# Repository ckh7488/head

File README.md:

# R5 로봇 헤드

R5는 코에 숨긴 카메라로 지나가는 사람을 보고, 눈이 먼저 움직인 뒤 목이 천천히 따라가는 **6축 해골 로봇**입니다. PC가 얼굴을 찾고 OpenRB-150이 모터 여섯 축을 제어합니다. 전시 모드에서는 눈을 깜빡이며, 턱은 별도 시연 모드에서 움직입니다.

현재 제작 자료는 **B26 기구와 A5 서보 허브** 기준입니다. P2S PETG HF 출력은 **18판·55개**입니다. 168단계 조립 경로를 CAD로 검사했으며, 최종 체결·배선과 구동은 P01–P08 실물 시험에서 확인합니다. [B26 제작 자료](mechanical/revisions/b26/) · [조립 절차](mechanical/revisions/b26/assembly.md)

## 제작 순서

| 순서 | 할 일 |
| --- | --- |
| 1. 출력 준비 | 핀·베어링·나사를 준비합니다. 한 번에 맡길 때는 **15번 링크 판**으로 바닥 접지를 확인한 뒤 **13번 턱 판**으로 큰 부품의 출력 상태를 확인합니다. [출력과 후가공](mechanical/revisions/b25/01-seoul-print.md) · [먼저 살 부품](mechanical/revisions/b25/02-order-before.md) |
| 2. 건식 맞춤 | 전원과 접착제 없이 끼움과 공구 접근을 봅니다. 턱을 연 채 오른쪽 받침과 요크 사이에 0.30 mm 틈새 게이지가 통과하는지 확인합니다. [건식 맞춤](mechanical/revisions/b25/01-seoul-print.md#출력물-후가공과-건식-맞춤) · [치수 선택용 게이지](mechanical/revisions/b25/fit-gauge.md) |
| 3. 모터·전장 구매 | 건식 맞춤을 마친 뒤 모터·카메라·A5 허브를 준비합니다. [시험 뒤 구매](mechanical/revisions/b25/03-order-after.md) · [A5 PCBA 발주](electronics/README.md#jlcpcb-밑면-실장) |
| 4. 허브 첫 통전 | 허브를 받침에 넣기 전에 작업대에서 확인합니다. 모터·OpenRB·퓨즈를 뺍니다. 무전원 도통 확인과 J2 잠금을 마친 뒤 입력 전압부터 확인합니다. [전원 실물 검수](electronics/README.md#전원-실물-검수) |
| 5. 조립과 보정 | 허브의 전원을 뽑고 조립·배선합니다. 무전원에서 배선을 확인하고, 전원을 켜서 한 축씩 보정합니다. [B26 조립 절차](mechanical/revisions/b26/assembly.md) · [구동과 보정](control/README.md) |
| 6. 실물 인수 | 완성품의 조립 상태, 움직임, 전압과 전원 복구를 확인합니다. [실물 시험 P01–P08](spec/bench.md#b25-실물-시험) |

## 주요 사양

| 항목 | B26 적용값 |
| --- | --- |
| 머리 외형과 환경 | 약 `160 × 166 × 167 mm`, 한국 실내 `−5–35 °C` |
| 3D 프린팅 | **Bambu Lab P2S** (0.4 mm 경화 노즐), **Bambu PETG HF** (65 °C 4–6시간 건조 · 2롤), 18판·55개 |
| 눈과 턱 (5 V) | ID1–ID3 `XL330-M077-T` × 3, ID6 `XL330-M288-T` × 1 |
| 목 (12 V) | ID4·ID5 `XL430-W250-T` × 2 |
| 카메라와 제어 | `U20CAM-1080P-S1`, `OpenRB-150` (USB 전원), `A5 서보 허브` |

## 파일과 기준

- [A5 회로도·PCB·3D 단일 HTML](web/b25/R5-B25-A5.html)
- [FreeCAD 조립본](mechanical/revisions/b26/R5-B26-Assembly.FCStd) · [P2S PETG HF 출력 프로젝트](mechanical/revisions/b26/R5-B26-P2S.3mf) · [B26 오프라인 3D 조립](web/b26/R5-B26-assembly.html) · [3D 조립·구동·배선 화면 만들기](web/README.md#b26-웹-화면)
- [1층 사람 요구사항](spec/user-spec.md) · [2층 수치 기준](spec/conditions.md) · [FDM 실수 모음집](spec/fdm-pitfalls.md) · [동작 인수 기준](spec/requirements.md)
- [기구 자료](mechanical/README.md) · [전장 자료](electronics/README.md) · [하드웨어 없이 테스트](control/README.md#하드웨어-없이-실행) · [이전 리비전](mechanical/revisions/)

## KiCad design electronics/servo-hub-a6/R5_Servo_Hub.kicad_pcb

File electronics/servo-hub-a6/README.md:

# B25 A6 서보 허브

전 부품을 직접 납땜하는 4층 시안입니다. 기판 앞쪽을 2 mm 늘려 70 × 37 mm로 만들고, 밑면의 보호 칩 세 개를 한 줄로 배치했습니다. H1–H4와 J1–J8의 위치·홀·핀 연결은 A5와 같습니다. [오프라인 뷰어](../../web/b25/R5-B25-A6.html) · [회로도](R5_Servo_Hub.kicad_sch) · [PCB](R5_Servo_Hub.kicad_pcb) · [전체 BOM](BOM.csv)

## 납땜과 주문

1. Gerber로 **FR-4 1.6 mm · 4층 · 외층 1 oz · 내층 0.5 oz · 녹색 · 무연 HASL** 생기판을 견적 냅니다. [Gerber·드릴](../fabrication/R5_Servo_Hub_A6-Gerbers.zip) · [JLCPCB 기판 규격](https://jlcpcb.com/capabilities/pcb-capabilities)
2. 밑면 SMD 12개를 먼저 납땜합니다. U1–U3은 다리가 보이는 **TPS25221DBVR, SOT-23-6, 피치 0.95 mm**입니다. 세 칩의 방향은 같으며 HTML의 밑면 그림에 1번 핀이 표시됩니다. R4–R6은 **30.9 kΩ, ±0.1%, ≤25 ppm/°C, 0805**, C3–C5는 **100 nF, 0805, 몸체 높이 1.45 mm 이하**입니다. [TI 데이터시트와 패키지 도면](https://www.ti.com/lit/ds/symlink/tps25221.pdf)
3. 윗면 관통홀 14개를 끼운 뒤 밑면에서 납땜합니다. XT30과 퓨즈 홀더에는 열 회복이 빠른 온도조절 인두와 2.4 mm 안팎의 평팁을 씁니다. F1·F2, 모터와 OpenRB를 뺀 채 5 V와 12 V 입력을 하나씩 검수합니다. [전원 실물 검수](../README.md#전원-실물-검수)

## 검사 결과

- KiCad ERC, DRC, 회로도와 PCB 일치 검사에서 위반 0건입니다.
- 기존 B25 FreeCAD 조립에서 확장한 기판과 새 밑면 SMD 9개의 외형을 넣고, 밑면 덮개 30 mm 하강 경로를 확인했습니다. 기판 외곽과 배치 공차를 포함한 검사에서 기판과 베이스의 겹침은 없었고, 새 부품과 덮개의 최소 간격은 **0.565 mm**였습니다. [B25 조립 CAD](../../mechanical/revisions/b25/R5-B25-Assembly.FCStd)
- 공칭 5 V와 카탈로그 정지전류를 동시에 적용한 보수적 모델에서 최저 모터 단자 전압은 **4.025 V**입니다. 같은 계산에서 A5는 **4.132 V**입니다. TPS25221 자체의 전형 저항은 70 mΩ로 TPS2557의 22 mΩ보다 높습니다. 1.47 A에서 칩 하나의 전압강하는 약 71 mV 늘고 전형 손실은 약 0.05 W에서 0.15 W로 늘어납니다. 칩의 권장 입력 상한은 6.5 V에서 5.5 V로 낮아집니다. 30.9 kΩ 설정의 데이터시트 전류 제한 범위는 1.626–1.907 A입니다. 첫 시제품에서 동작 중 전압, 보호 칩 온도와 전류 제한에 걸리는지 확인합니다. [P07 실물 시험](../../spec/bench.md#p07-카메라-왕복과-전원)

기판 제작 파일은 첫 명령으로 만듭니다. HTML을 재생성하려면 결과 Gerber ZIP을 `electronics/fabrication/`에 두고 KiCad 9의 3D 모델과 `npm ci --prefix web`을 준비합니다. XT30 STEP은 A5 문서의 원본 모델 규격을 따릅니다. [XT30 STEP 좌표](../servo-hub-a5/#검증)

```sh
/usr/bin/python3 electronics/export.py servo-hub-a6
/usr/bin/python3 electronics/power_check.py --hub-revision A6
/usr/bin/python3 web/wiring-review/a4/build.py --hub-revision A6 --xt30-step /path/to/XT30PW-M.step build/R5-B25-A6.html
```

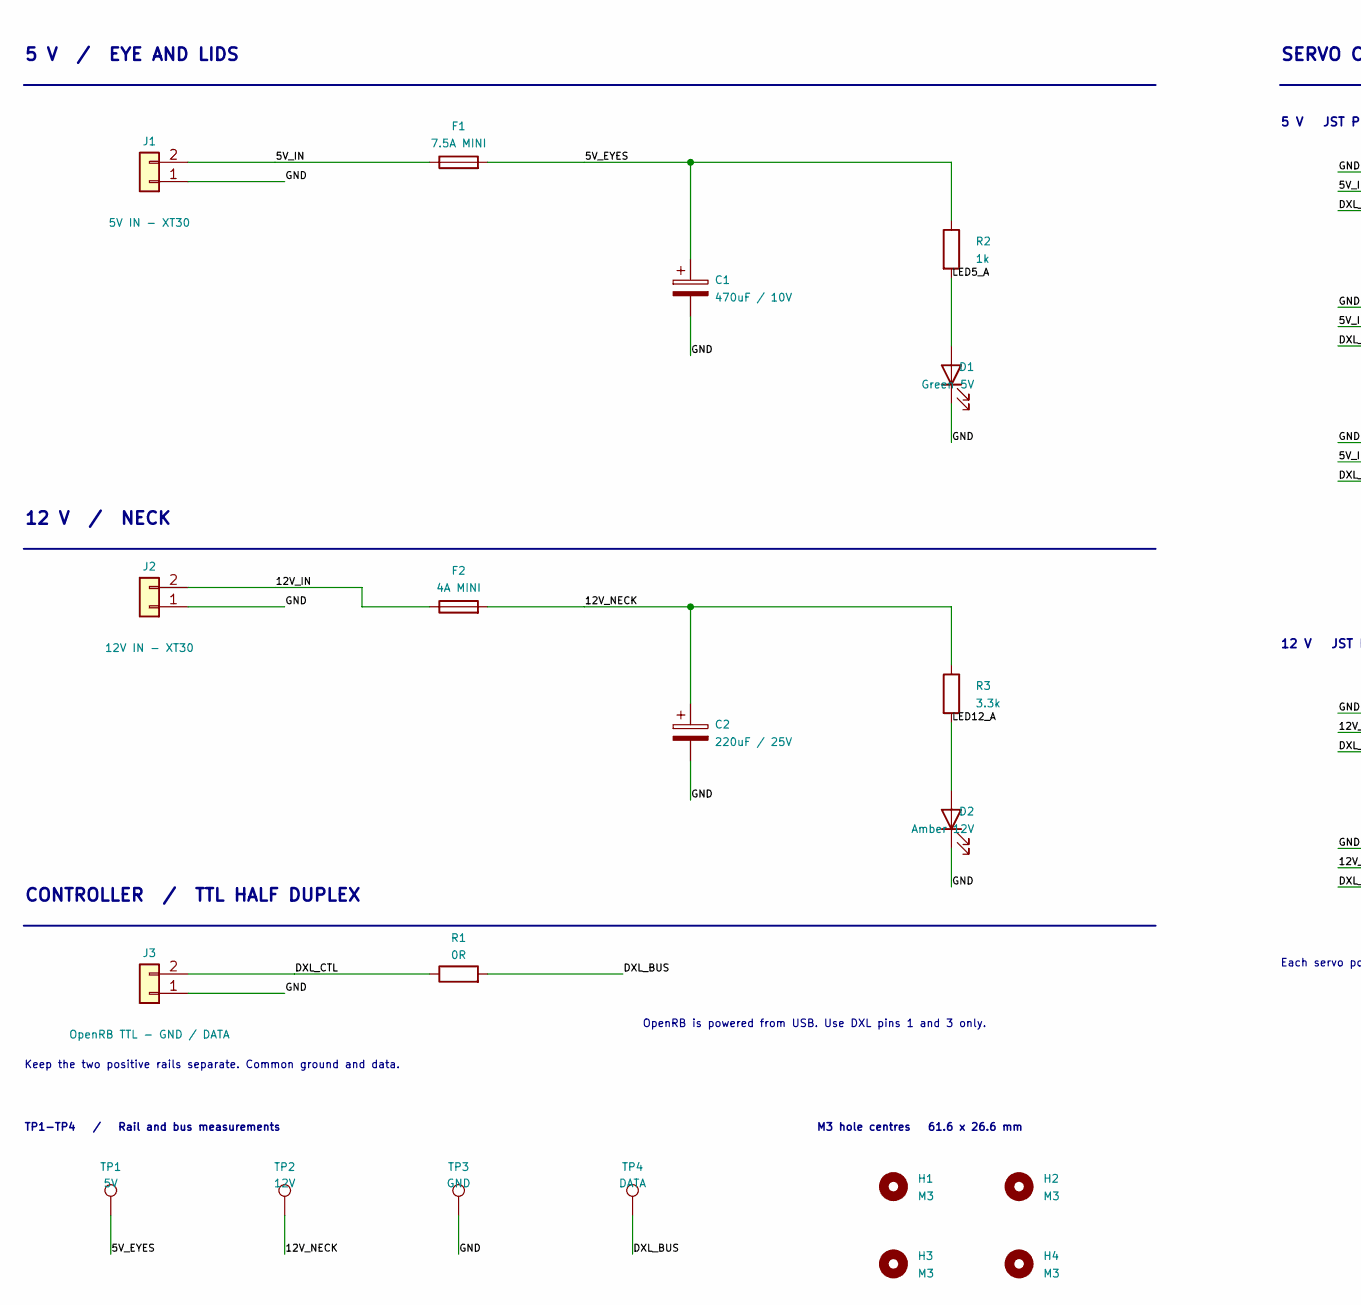
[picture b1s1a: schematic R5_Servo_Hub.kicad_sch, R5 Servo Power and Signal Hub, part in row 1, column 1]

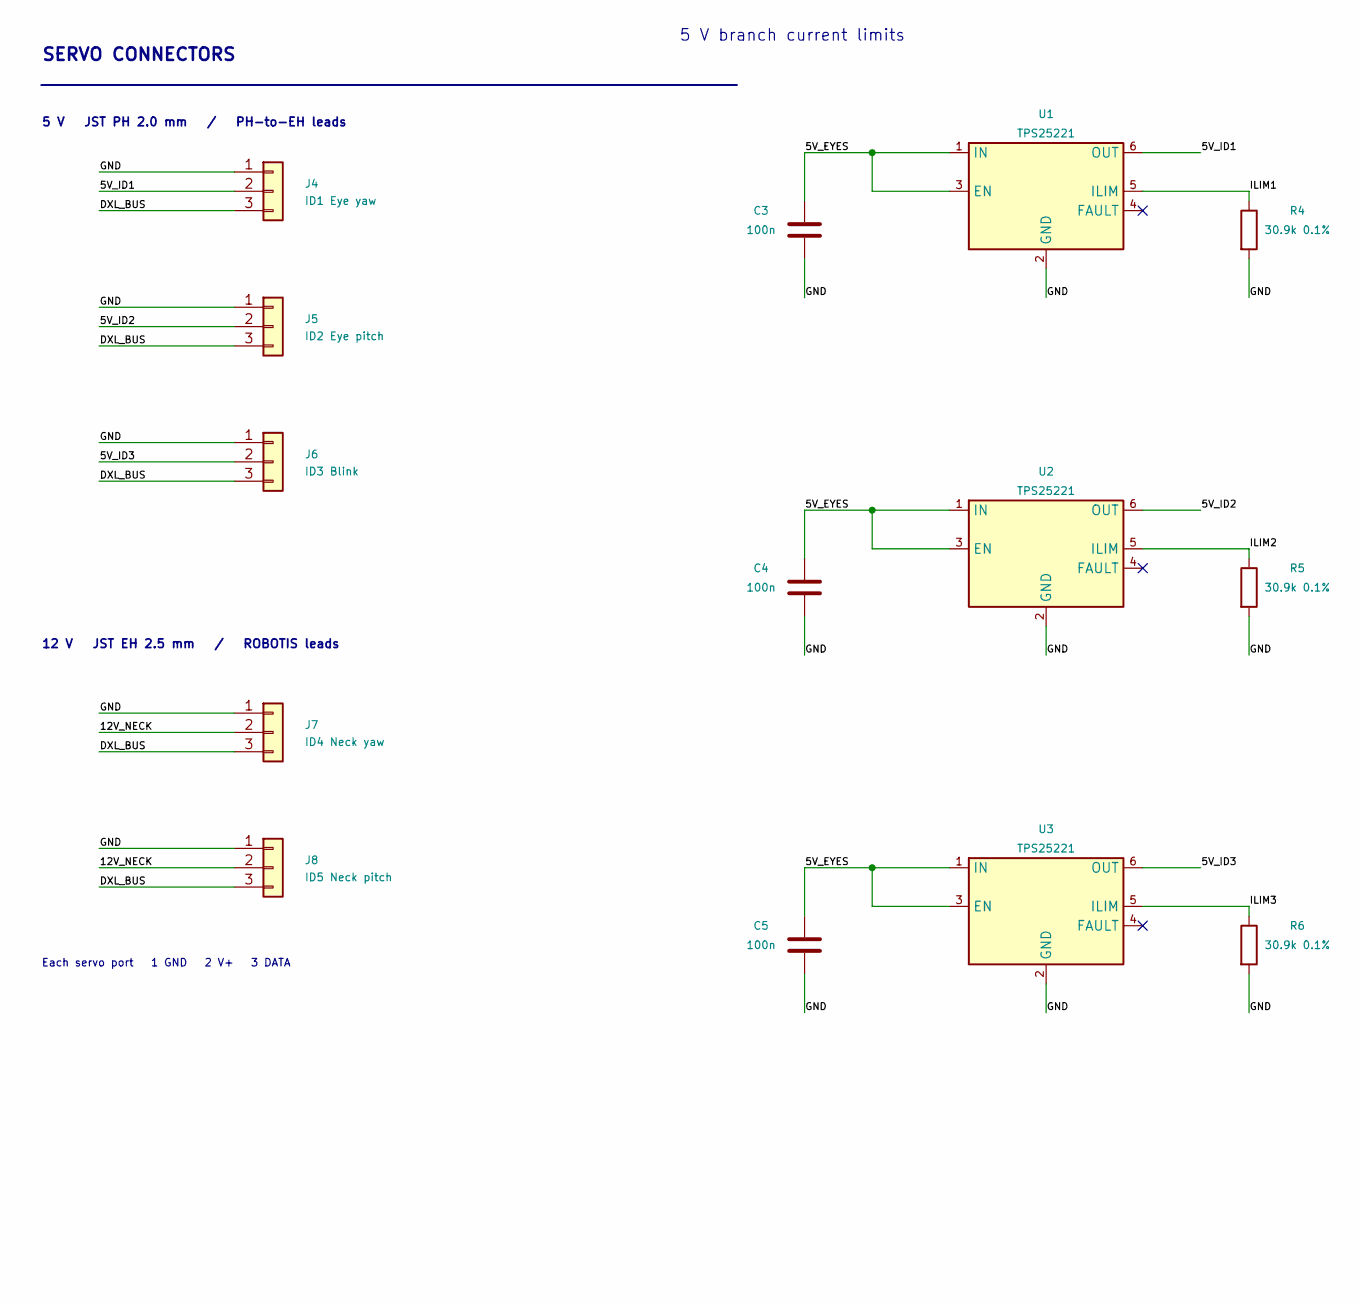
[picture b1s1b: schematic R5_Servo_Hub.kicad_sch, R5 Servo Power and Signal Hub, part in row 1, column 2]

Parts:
C1: 470uF / 10V; CP_Radial_D8.0mm_P3.50mm
C2: 220uF / 25V; CP_Radial_D8.0mm_P3.50mm
C3, C4, C5: 100n; C_0805_2012Metric
D1: Green 5V; LED_D3.0mm
D2: Amber 12V; LED_D3.0mm
F1: 7.5A MINI; Fuseholder_Blade_Mini_Keystone_3568
F2: 4A MINI; Fuseholder_Blade_Mini_Keystone_3568
H1, H2, H3, H4: M3; MountingHole_3.2mm_M3
J1: 5V IN - XT30; AMASS_XT30PW-M_1x02_P5.00mm_Horizontal_J1
J2: 12V IN - XT30; AMASS_XT30PW-M_1x02_P5.00mm_Horizontal
J3: OpenRB TTL - GND / DATA; JST_PH_B2B-PH-K_1x02_P2.00mm_Vertical
J4: ID1 Eye yaw; JST_PH_B3B-PH-K_1x03_P2.00mm_Vertical
J5: ID2 Eye pitch; JST_PH_B3B-PH-K_1x03_P2.00mm_Vertical
J6: ID3 Blink; JST_PH_B3B-PH-K_1x03_P2.00mm_Vertical
J7: ID4 Neck yaw; JST_EH_B3B-EH-A_1x03_P2.50mm_Vertical
J8: ID5 Neck pitch; JST_EH_B3B-EH-A_1x03_P2.50mm_Vertical
R1: 0R; R_1206_3216Metric
R2: 1k; R_1206_3216Metric
R3: 3.3k; R_0805_2012Metric
R4, R5, R6: 30.9k 0.1%; R_0805_2012Metric
TP1: 5V; TestPoint_THTPad_D2.0mm_Drill1.0mm
TP2: 12V; TestPoint_THTPad_D2.0mm_Drill1.0mm
TP3: GND; TestPoint_THTPad_D2.0mm_Drill1.0mm
TP4: DATA; TestPoint_THTPad_D2.0mm_Drill1.0mm
U1, U2, U3: TPS25221; SOT-23-6

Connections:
/5V_EYES: C1.1, C3.1, C4.1, C5.1, F1.2, R2.1, TP1.1, U1.1 (IN), U1.3 (EN), U2.1 (IN), U2.3 (EN), U3.1 (IN), U3.3 (EN)
/5V_ID1: J4.2, U1.6 (OUT)
/5V_ID2: J5.2, U2.6 (OUT)
/5V_ID3: J6.2, U3.6 (OUT)
/5V_IN: F1.1, J1.2
/12V_IN: F2.1, J2.2
/12V_NECK: C2.1, F2.2, J7.2, J8.2, R3.1, TP2.1
/DXL_BUS: J4.3, J5.3, J6.3, J7.3, J8.3, R1.2, TP4.1
/DXL_CTL: J3.2, R1.1
/GND: C1.2, C2.2, C3.2, C4.2, C5.2, D1.1 (K), D2.1 (K), J1.1, J2.1, J3.1, J4.1, J5.1, J6.1, J7.1, J8.1, R4.2, R5.2, R6.2, TP3.1, U1.2 (GND), U2.2 (GND), U3.2 (GND)
/ILIM1: R4.1, U1.5 (ILIM)
/ILIM2: R5.1, U2.5 (ILIM)
/ILIM3: R6.1, U3.5 (ILIM)
/LED5_A: D1.2 (A), R2.2
/LED12_A: D2.2 (A), R3.2

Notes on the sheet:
5 V / EYE AND LIDS
12 V / NECK
CONTROLLER / TTL HALF DUPLEX
SERVO CONNECTORS
5 V JST PH 2.0 mm / PH-to-EH leads
12 V JST EH 2.5 mm / ROBOTIS leads
Each servo port 1 GND 2 V+ 3 DATA
TP1-TP4 / Rail and bus measurements
M3 hole centres 61.6 x 26.6 mm
OpenRB is powered from USB. Use DXL pins 1 and 3 only.
Keep the two positive rails separate. Common ground and data.
5 V branch current limits

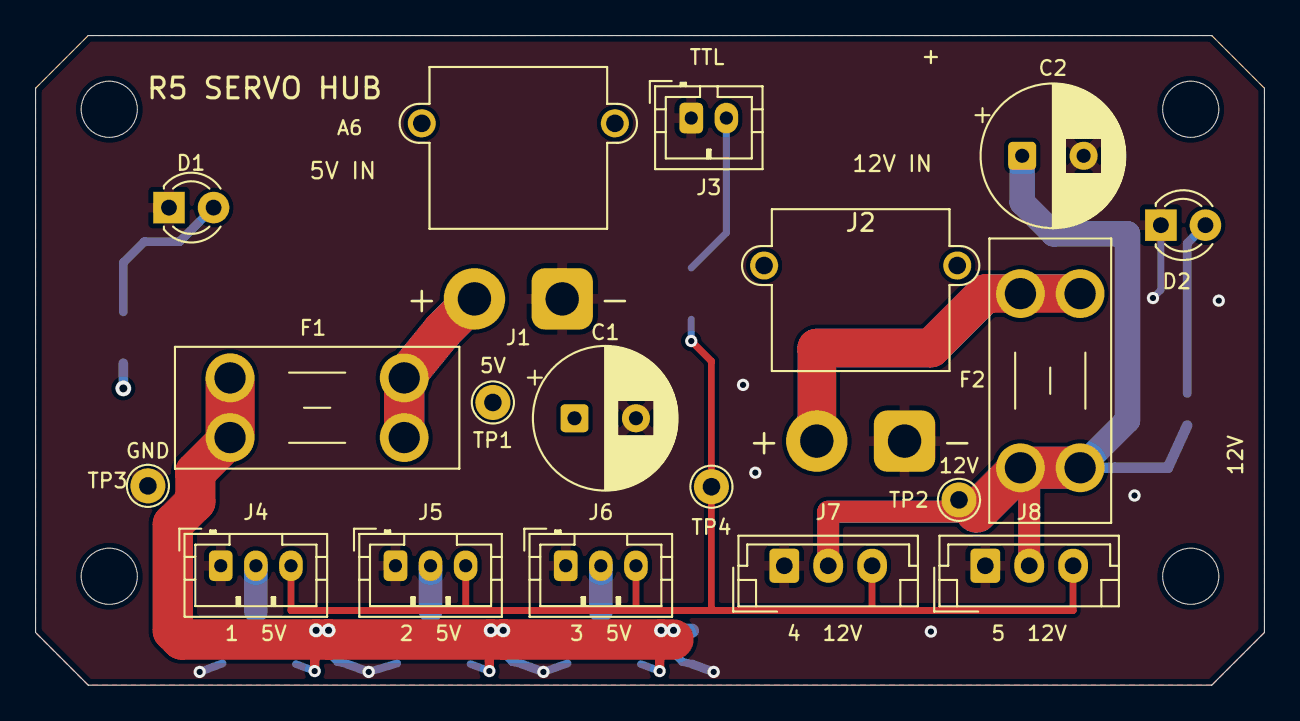
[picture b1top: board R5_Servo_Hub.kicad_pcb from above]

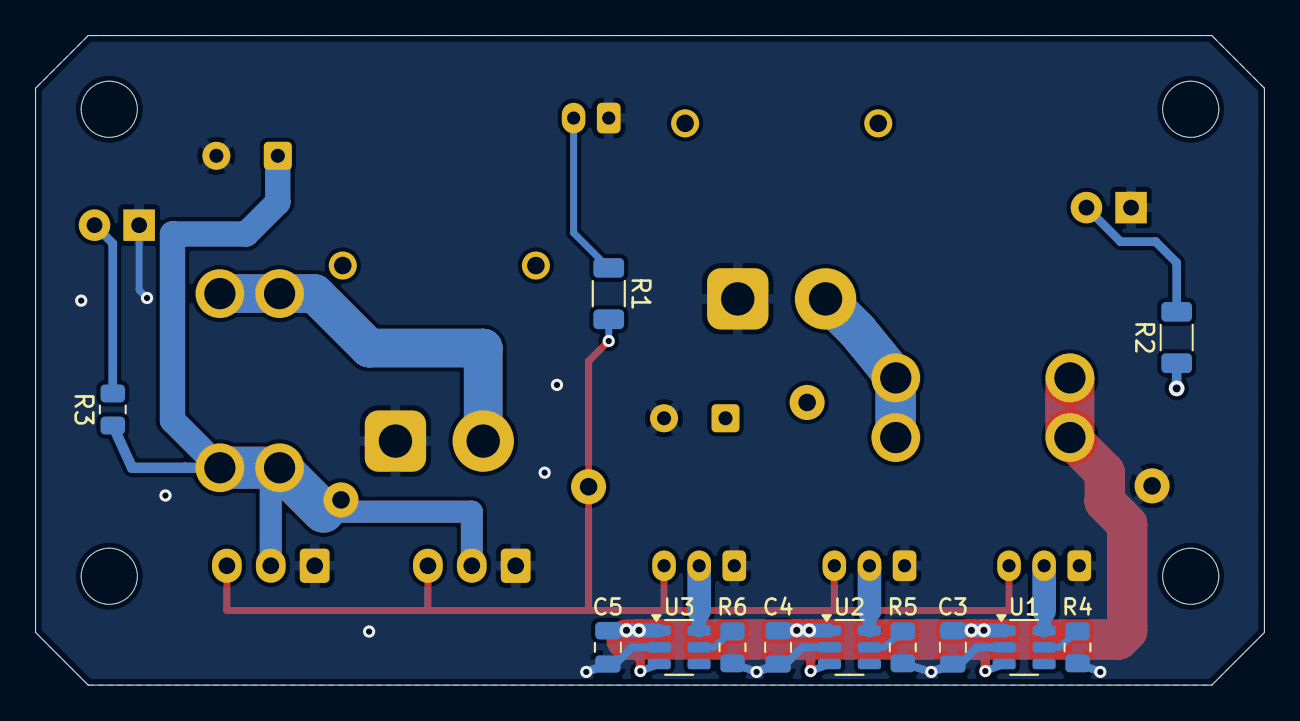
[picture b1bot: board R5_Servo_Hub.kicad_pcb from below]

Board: 4 copper layers, 70.0 x 37.0 mm, 34 parts (12 on the bottom side), 15 nets.

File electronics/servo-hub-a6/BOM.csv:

Ref,Value,Footprint,Populate,Part or buying specification,Notes
C1,470uF / 10V,Capacitor_THT:CP_Radial_D8.0mm_P3.50mm,YES,Panasonic EEU-FR1A471,"470 µF / 10 V, Ø8 × 11.5 mm, P3.5 mm. Match polarity."
C2,220uF / 25V,Capacitor_THT:CP_Radial_D8.0mm_P3.50mm,YES,Panasonic EEU-FR1E221,"220 µF / 25 V, Ø8 × 11.5 mm, P3.5 mm. Match polarity."
C3,100n,Capacitor_SMD:C_0805_2012Metric,YES,"100 nF X7R ±10% 50 V, 0805","Body height 1.45 mm max, 50 V, X7R, ±10% local input bypass"
C4,100n,Capacitor_SMD:C_0805_2012Metric,YES,"100 nF X7R ±10% 50 V, 0805","Body height 1.45 mm max, 50 V, X7R, ±10% local input bypass"
C5,100n,Capacitor_SMD:C_0805_2012Metric,YES,"100 nF X7R ±10% 50 V, 0805","Body height 1.45 mm max, 50 V, X7R, ±10% local input bypass"
D1,Green 5V,LED_THT:LED_D3.0mm,YES,3 mm diffused through-hole LED Green,"P2.54 mm, cathode pin 1"
D2,Amber 12V,LED_THT:LED_D3.0mm,YES,3 mm diffused through-hole LED Amber,"P2.54 mm, cathode pin 1"
F1,7.5A MINI,Fuse:Fuseholder_Blade_Mini_Keystone_3568,YES,Keystone 3568 + Littelfuse 029707.5L (7.5 A),Common 5 V feed
F2,4A MINI,Fuse:Fuseholder_Blade_Mini_Keystone_3568,YES,Keystone 3568 + Littelfuse 0297004.WXNV (4 A),12 V branch
H1,M3,MountingHole:MountingHole_3.2mm_M3,NATIVE,Bare pad or drilled mounting hole,No part
H2,M3,MountingHole:MountingHole_3.2mm_M3,NATIVE,Bare pad or drilled mounting hole,No part
H3,M3,MountingHole:MountingHole_3.2mm_M3,NATIVE,Bare pad or drilled mounting hole,No part
H4,M3,MountingHole:MountingHole_3.2mm_M3,NATIVE,Bare pad or drilled mounting hole,No part
J1,5V IN - XT30,R5_Hub:AMASS_XT30PW-M_1x02_P5.00mm_Horizontal_J1,YES,Amass XT30PW-M,"Pad 2 positive, pad 1 GND"
J2,12V IN - XT30,R5_Hub:AMASS_XT30PW-M_1x02_P5.00mm_Horizontal,YES,AMASS XT30PW-M,"Pad 2 positive, pad 1 GND. Mate with captive labeled 12 V XT30U-F."
J3,OpenRB TTL - GND / DATA,R5_Hub:JST_PH_B2B-PH-K_1x02_P2.00mm_Vertical,YES,JST B2B-PH-K-S,"EH1 to PH1, EH3 to PH2, no wire on EH2"
J4,ID1 Eye yaw,R5_Hub:JST_PH_B3B-PH-K_1x03_P2.00mm_Vertical,YES,JST B3B-PH-K-S,"5 V output, fit PH-to-EH lead"
J5,ID2 Eye pitch,R5_Hub:JST_PH_B3B-PH-K_1x03_P2.00mm_Vertical,YES,JST B3B-PH-K-S,"5 V output, fit PH-to-EH lead"
J6,ID3 Blink,R5_Hub:JST_PH_B3B-PH-K_1x03_P2.00mm_Vertical,YES,JST B3B-PH-K-S,"5 V output, fit PH-to-EH lead"
J7,ID4 Neck yaw,Connector_JST:JST_EH_B3B-EH-A_1x03_P2.50mm_Vertical,YES,JST B3B-EH-A,12 V output
J8,ID5 Neck pitch,Connector_JST:JST_EH_B3B-EH-A_1x03_P2.50mm_Vertical,YES,JST B3B-EH-A,12 V output
R1,0R,Resistor_SMD:R_1206_3216Metric,YES,Uniroyal 1206W4F0000T5E,"0 Ω data link, hand solder on bottom"
R2,1k,Resistor_SMD:R_1206_3216Metric,YES,Uniroyal 1206W4F1001T5E,"1 kΩ, 1%, 250 mW, hand solder on bottom"
R3,3.3k,Resistor_SMD:R_0805_2012Metric,YES,Uniroyal 0805W8F3301T5E,"3.3 kΩ, 1%, 125 mW, hand solder on bottom"
R4,30.9k 0.1%,Resistor_SMD:R_0805_2012Metric,YES,"30.9 kΩ, ±0.1%, ≤25 ppm/°C, 0805",Per-channel current limit
R5,30.9k 0.1%,Resistor_SMD:R_0805_2012Metric,YES,"30.9 kΩ, ±0.1%, ≤25 ppm/°C, 0805",Per-channel current limit
R6,30.9k 0.1%,Resistor_SMD:R_0805_2012Metric,YES,"30.9 kΩ, ±0.1%, ≤25 ppm/°C, 0805",Per-channel current limit
TP1,5V,TestPoint:TestPoint_THTPad_D2.0mm_Drill1.0mm,NATIVE,Bare pad or drilled mounting hole,No part
TP2,12V,TestPoint:TestPoint_THTPad_D2.0mm_Drill1.0mm,NATIVE,Bare pad or drilled mounting hole,No part
TP3,GND,TestPoint:TestPoint_THTPad_D2.0mm_Drill1.0mm,NATIVE,Bare pad or drilled mounting hole,No part
TP4,DATA,TestPoint:TestPoint_THTPad_D2.0mm_Drill1.0mm,NATIVE,Bare pad or drilled mounting hole,No part
U1,TPS25221,Package_TO_SOT_SMD:SOT-23-6,YES,Texas Instruments TPS25221DBVR,J4 safety current limiter
U2,TPS25221,Package_TO_SOT_SMD:SOT-23-6,YES,Texas Instruments TPS25221DBVR,J5 safety current limiter
U3,TPS25221,Package_TO_SOT_SMD:SOT-23-6,YES,Texas Instruments TPS25221DBVR,J6 safety current limiter

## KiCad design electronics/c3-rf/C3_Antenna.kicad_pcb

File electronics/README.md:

# B25 서보 허브 A5

B25 제작에는 **A5**를 사용합니다. 70 × 35 mm 4층 보드의 밑면 SMD 12개는 공장에 맡기고 윗면 관통홀 부품 14개는 직접 납땜합니다. [A5 회로도·PCB·3D](../web/b25/R5-B25-A5.html) · [시험 뒤 구매 목록](../mechanical/revisions/b25/03-order-after.md)

받침 뒤의 **XT30은 5 V**, **XT60은 12 V**입니다. 작업대에서 무전원 검사를 마치고, 첫 통전 전에 내부 J2 잠금쇠를 고정합니다. [B25 조립](../mechanical/revisions/b25/assembly.md#전원-커넥터와-배선) · [핀별 배선도](https://r5-b1-review.ckh.chatgpt.site/b25/wiring/diagram/)

| 작업 | 확인할 항목 |
| --- | --- |
| [A5 발주](#jlcpcb-밑면-실장) | 4층 무연 HASL, 밑면 12개, U1–U3의 1번 핀 |
| [첫 통전](#전원-실물-검수) | 양쪽 퓨즈를 빼고 5 V와 12 V 입력을 하나씩 확인 |
| [모터와 OpenRB 결선](#허브-단자와-배선) | 모터별 전원 핀과 J3의 GND·DATA |
| [하부 덮개 정비](#하부-덮개-정비) | 두 어댑터와 USB를 분리한 뒤 뒤쪽 XT60 서비스 플러그 사용 |
| [구동 중 전원 확인](#구동-중-전원-확인) | 어댑터 출력과 각 모터 단자의 최저·최고 전압 |

## A5 발주

### JLCPCB 밑면 실장

건식 맞춤 뒤 **70 × 35 mm · FR-4 1.6 mm · 4층 · 외층 1 oz · 내층 0.5 oz · 녹색 · 무연 HASL**로 견적을 받습니다. **Economic PCBA, Bottom, 실장 2장**을 선택합니다. U1–U3의 바닥 GND 패드는 X-ray 검사 범위와 견적을 확인합니다. [Gerber·드릴 ZIP](fabrication/R5_Servo_Hub_A5-Gerbers.zip) · [실장 BOM](fabrication/R5_Servo_Hub_A5-JLCPCB-BOM.csv) · [실장 CPL](fabrication/R5_Servo_Hub_A5-JLCPCB-CPL.csv) · [JLCPCB 실장 규격](https://jlcpcb.com/capabilities/pcb-assembly-capabilities)

CPL에서 U1–U3은 모두 0°입니다. 밑면 미리보기에서 각 칩의 몸체 점을 기판의 1번 패드 옆 표시와 대조합니다. 받은 기판에 J1–J8, F1·F2 홀더, C1·C2 및 D1·D2를 윗면에서 끼우고 밑면에서 납땜합니다. C1·C2의 극성과 J1·J2의 방향을 먼저 확인하세요. [A5 구매와 손납땜](servo-hub-a5/README.md#손납땜) · [A5 전체 BOM](servo-hub-a5/BOM.csv)

## 전원과 배선

### 전원 실물 검수

**허브를 받침에 넣기 전에 작업대에서 확인합니다.** 내부 J1·J2는 같은 XT30이므로 12 V 플러그가 J1에도 들어갑니다. F1이 장착된 상태에서 J1에 12 V를 넣으면 모터를 빼 두어도 TPS2557의 절대최대 **7 V**와 C1의 정격 **10 V**를 넘어 부품이 손상될 수 있습니다. F1은 과전류 퓨즈입니다. 두 퓨즈를 뺀 채 아래 순서로 입력을 확인합니다. [TPS2557 데이터시트 7.1·7.3절](https://www.ti.com/lit/ds/symlink/tps2557.pdf)

1. **두 어댑터를 AC와 하네스에서 분리하고 USB·모터·OpenRB를 뺍니다. F1·F2 퓨즈도 뺍니다.** 뒤 `12 V SERVICE` XT60을 분리합니다. W3/W4 양끝은 `J1 · 5 V`, W8/W9 양끝은 `J2 · 12 V`로 표시합니다. 뒤쪽 XT60 두 곳은 `12 V IN`과 `12 V SERVICE`로 표시합니다. 각 어댑터는 하네스에 연결하기 전에 DC 출력과 극성을 재고 AC에서 분리합니다.
2. 무전원에서 J1·J2를 꽂고 허브를 하부 덮개에 고정합니다. 분리된 **가동 XT60의 +는 F2 입력 접점에만**, −는 **TP3(GND)**에 도통되는지 확인합니다. 외부 5 V XT30의 +는 **F1 입력 접점에만**, −는 **TP3**에 도통되어야 합니다. 두 입력 양극끼리와 GND 사이의 단락도 확인합니다. **J2 잠금쇠를 H2·H4에 조인 뒤** 플러그 뒤턱이 걸려 있는지 확인합니다. [P02의 무전원 잠금 확인](../spec/bench.md#p02-내부-j2-잠금쇠)을 마치면 서비스 XT60을 연결합니다.
3. **퓨즈를 뺀 채** 검정 리드를 `GND` 실크가 있는 TP3에 댑니다. 어댑터를 하나씩 켜서 F1 입력에 +5 V, F2 입력에 +12 V가 각각 나타나는지 확인합니다. 전압이 다른 입력에 나타나거나 극성이 다르면 전원을 분리하고 처음부터 확인합니다. 5 V를 켜면 F1 앞에 분기된 턱 배선에도 전압이 걸립니다.
4. 두 어댑터를 AC에서 분리하고 입력이 0 V로 내려가면 **F1 7.5 A, F2 4 A**를 넣습니다. 모터·OpenRB·USB를 분리한 채 한 계통씩 확인합니다.

   | 연결할 어댑터 | TP3(GND) 기준 | 모터를 꽂기 전 출력 핀 2 |
   | --- | --- | --- |
   | 5 V만 | TP1 약 +5 V | J4–J6 약 +5 V, 2 A 인라인 퓨즈 뒤 턱 ID6 EH 약 +5 V |
   | 12 V만 | TP2 약 +12 V | J7·J8 약 +12 V |

5. 전원을 분리하고 전압이 0 V가 되면 아래 핀을 대조해 OpenRB와 모터를 연결합니다. **일상 정비는 뒤쪽 XT60에서 분리합니다.** 내부 J2 잠금쇠를 푸는 작업에서는 1번부터 다시 확인합니다. [B25 조립 순서](../mechanical/revisions/b25/assembly.md#전원-커넥터와-배선)

### 허브 단자와 배선

새로 재단하는 선의 색은 **+5 V·+12 V 빨강, GND 검정, 모터 DATA 흰색**으로 고정합니다. 두 전압의 양극 색이 같으므로 선 양끝의 J1·J2 및 전압 라벨로 구분합니다. 카메라 USB의 접합부 표식은 **VBUS 빨강, D− 흰색, D+ 초록, GND 검정**입니다. 순정 플러그와 선재의 도체는 절단 전 도통으로 식별합니다. [핀과 선의 색·길이](https://r5-b1-review.ckh.chatgpt.site/b25/wiring/diagram/) · [하네스 재단표](../mechanical/WIRING-CUT-LIST.csv)

| 단자 | 연결 |
| --- | --- |
| J1 5 V 입력 | 패드 2는 +, 1은 GND. W3/W4의 XT30U-F 연결 |
| J2 12 V 목 전원 입력 | 패드 2에 W8 적색(+), 패드 1에 W9 흑색(GND). XT30U-F를 J2 쪽 잠금쇠로 고정 |
| J3 OpenRB | W10은 **OpenRB EH 1(GND) → J3 PH 1**, W11은 **OpenRB EH 3(DATA) → J3 PH 2**. **OpenRB EH 2(VDD)는 금속 단자 없이 비움** |
| J4–J6 | ID 1–3. PH 1 GND / 2 **개별 전류 제한 5 V** / 3 DATA |
| J7·J8 | ID 4·5. EH 1 GND / 2 **12 V 목 전원** / 3 DATA |
| 턱 ID 6 | 어댑터 5 V에서 **2 A 인라인 퓨즈**를 거쳐 EH 2. 입력 GND는 EH 1, J6 DATA는 EH 3에 분기 |

OpenRB는 USB를 뽑은 상태에서 점퍼를 **USB(VIN)** 쪽에 놓습니다. 나사식 VIN 단자를 비워 두고 제어기만 USB로 공급합니다. 무전원에서 W10·W11의 도통, 두 선 사이의 단락 여부, EH 2에 금속 단자가 없는지 확인한 뒤 J3를 연결합니다. 5 V와 12 V 목 전원은 GND·DATA를 공유하고 양극 배선은 각각 독립입니다. [OpenRB 전원 점퍼](https://emanual.robotis.com/docs/en/parts/controller/openrb-150/#power-source-jumper) · [포트 핀 배치](https://emanual.robotis.com/docs/en/parts/controller/openrb-150/#dynamixel-ports)

5 V 배선에는 XT30U-F 두 개와 XT30U-M 한 개를 씁니다. F 한 개는 5 V 전원 꼬리, 다른 한 개는 J1 쪽 W3/W4에 씁니다. 외부 5 V XT30과 12 V XT60은 서로 다른 외형과 단자 간격(각각 5.0 mm와 7.2 mm)으로 구분합니다. [AMASS XT30U](https://www.china-amass.com/biao/268.html) · [AMASS XT60U](https://www.china-amass.com/biao/288.html)

12 V 어댑터의 DC 출력 리드에는 **XT60U-F 한 개**를 납땜합니다. 어댑터의 출력 극성을 멀티미터로 확인하고, AC에서 분리한 뒤 XT60U-F 몸체의 +·− 표기에 맞춥니다. 두 컵을 각각 절연하고 **12 V IN** 라벨을 붙입니다. 받침의 XT60U-M에서 W6·W7이 시작됩니다. [12 V 고정선 조립](../mechanical/revisions/b25/j2-supply-delta.md) · [하네스 재단표](../mechanical/WIRING-CUT-LIST.csv)

### 하부 덮개 정비

두 어댑터와 USB를 뽑고 받침을 지지합니다. 뒤쪽 **`12 V SERVICE` XT60** 플러그를 똑바로 빼서 아래 대기 위치로 내린 뒤, 허브와 하부 덮개를 함께 내립니다. 내부 J2는 작업대에서 J2 쪽 M3×12 두 개를 풀어 분리합니다. 다시 닫을 때 선의 눌림, 커넥터 체결과 극성을 무전원에서 확인합니다. 내부 J1 또는 J2를 분리했다면 위의 [전원 실물 검수](#전원-실물-검수)를 다시 수행합니다. [B25 덮개·배선 절차](../mechanical/revisions/b25/assembly.md#전원-커넥터와-배선) · [3D 배선·정비](https://r5-b1-review.ckh.chatgpt.site/b25/wiring/)

`12 V SERVICE` 가동 플러그 XT60U-M의 제조사 권장 선은 12 AWG입니다. B25의 W8·W9는 18 AWG이므로 실제 컵 깊이로 탈피 길이를 정하고, 컵과 도체 모두에 납이 잘 젖었는지 확인합니다. 식힌 뒤 각 선을 가볍게 당겨 접합을 확인하고, 두 컵을 각각 열수축 튜브로 절연합니다. 플러그를 뺄 때 몸체를 잡고 가동선 루프를 받쳐 접합부의 당김을 줄입니다. 통전 전 극성과 단락, P08에서 절연부의 눌림과 당김을 확인합니다. [AMASS XT60U-M 사양](https://images.100y.com.tw/pdf_file/AMASS-XT60U.pdf) · [B25 정비 리드 조립](../mechanical/revisions/b25/j2-disconnect.md#결선과-남은-검증)

### 구동 중 전원 확인

검사 조건 14절의 실내 환경에서 받침을 수평으로 놓습니다. 목을 받치고 보정한 뒤 한 축씩 처음 구동합니다. 추적·깜빡임·별도 턱 시험에서 어댑터의 DC 출력과 각 모터 단자 전압을 기록합니다. 기동·급감속의 순간 전압을 보려면 오실로스코프로 최저·최고를 기록합니다. XL430의 제조사 작동 범위 상한은 12.0 V입니다. P07에서 OpenRB를 재시작한 뒤 토크 해제도 확인합니다. [OpenRB와 모터 보정](../control/README.md#openrb와-모터) · [검사 조건 14절](../spec/conditions.md#14-전원과-환경) · [P07 실물 시험](../spec/bench.md#b25-실물-시험)

모터 GND는 TTL DATA의 기준이자 전원 전류의 귀환 경로입니다. 전류가 급변하면 같은 GND 선의 전압 강하가 순간적으로 변해, 모터가 보는 DATA 전압이 흔들릴 수 있습니다. DATA와 해당 GND를 가까이 묶고 긴 공급선과 나란히 가는 구간을 줄입니다. 구동 중 통신 오류나 리셋이 보이면 해당 모터에서 **3번 DATA와 2번 전원**을 각각 **1번 GND** 기준으로 봅니다. 허브와 모터 간 GND 전위차를 직접 비교할 때는 차동 프로브를 사용합니다. [ROBOTIS 핀 배치](https://emanual.robotis.com/docs/en/parts/controller/openrb-150/#dynamixel-ports) · [배선도](https://r5-b1-review.ckh.chatgpt.site/b25/wiring/diagram/#ground)

U1–U3의 61.9 kΩ 설정에서 TI 특성표의 출력 제한은 **1.590 / 1.785 / 1.960 A**(최소 / 대표 / 최대)입니다. 저항값에 따른 근사식의 하한은 약 **1.54 A**이고 XL330의 5.0 V 공칭 정지 전류는 **1.47 A**입니다. 과전류 시 출력 전압이 내려가고, 과부하가 계속되면 온도에 따라 차단과 재시동을 반복할 수 있습니다. **FAULT 8번은 미연결**이라 LED와 OpenRB에 채널별 경보가 없습니다. 눈·눈꺼풀 기동에서 출력이 떨어지거나 모터가 리셋되면 TP1과 해당 J4–J6의 2번 핀을 비교하고 해당 채널의 전류와 온도를 확인합니다. TI는 출력의 과도 전류가 클 때 개별 출력 커패시터를 권장하며, A5의 개별 커패시터 C3–C5는 입력에 있습니다. J7·J8의 12 V는 공통 F2 4 A로 보호되므로 P08에서 두 분기 배선의 피복과 눌림을 확인합니다. [TPS2557 특성표·과전류 동작·설정식](https://www.ti.com/lit/ds/symlink/tps2557.pdf) · [XL330 사양](https://emanual.robotis.com/docs/en/dxl/x/xl330-m077/#specifications) · [A5 회로도](servo-hub-a5/R5_Servo_Hub.kicad_sch)

## 제작 치수와 전원 계산

J1·J2는 **5.00 mm 피치 XT30PW-M**입니다. 각 자리의 단자홀은 Ø1.90 mm 두 개, 고정홀은 Ø1.00 mm 두 개입니다. [AMASS XT30PW-M 도면](https://www.tme.eu/Document/6eb2005a51a52592b3f19e8a450c54c8/XT30PW-M.pdf)

공칭 5.0 V·12 V와 모터 카탈로그 정지전류를 적용한 A5 계산에서 최저 모터 단자 전압은 **J4 4.132 V, J8 11.460 V**입니다. 조립된 배선의 접촉저항, 어댑터의 부하 조정률과 순간 전압은 P07에서 측정합니다. [A5 계산과 검사 범위](servo-hub-a5/README.md#검증) · [P07 실물 시험](../spec/bench.md#b25-실물-시험)

## 재현

저장소 루트에서 KiCad 9의 `kicad-cli`와 `pcbnew`가 설치된 Python으로 실행합니다. 발주 파일은 `build/electronics/servo-hub-a5/`에 생성됩니다. [A5 HTML 재현](servo-hub-a5/README.md#검증)

```sh
/usr/bin/python3 electronics/power_check.py --hub-revision A5
/usr/bin/python3 electronics/export.py servo-hub-a5
```

## 이전 전장 기록

- [A4 2층 원본](servo-hub/) · [A4 발주·검증 이력](https://github.com/ckh7488/head/blob/b19aada/electronics/README.md#a4-발주) · [A3 제작 기록](fabrication/R5_Servo_Hub_A3-Gerbers.zip)
- [A6 전량 손납땜 시안](servo-hub-a6/) · [C3 별도 RF 실험](c3-rf/) · [외부 전원 보호 시안 계산](https://github.com/ckh7488/head/blob/9c024361d586ff5ea582cbac3e1328d40d5b0c65/electronics/README.md#외부-전원-보호-계산)

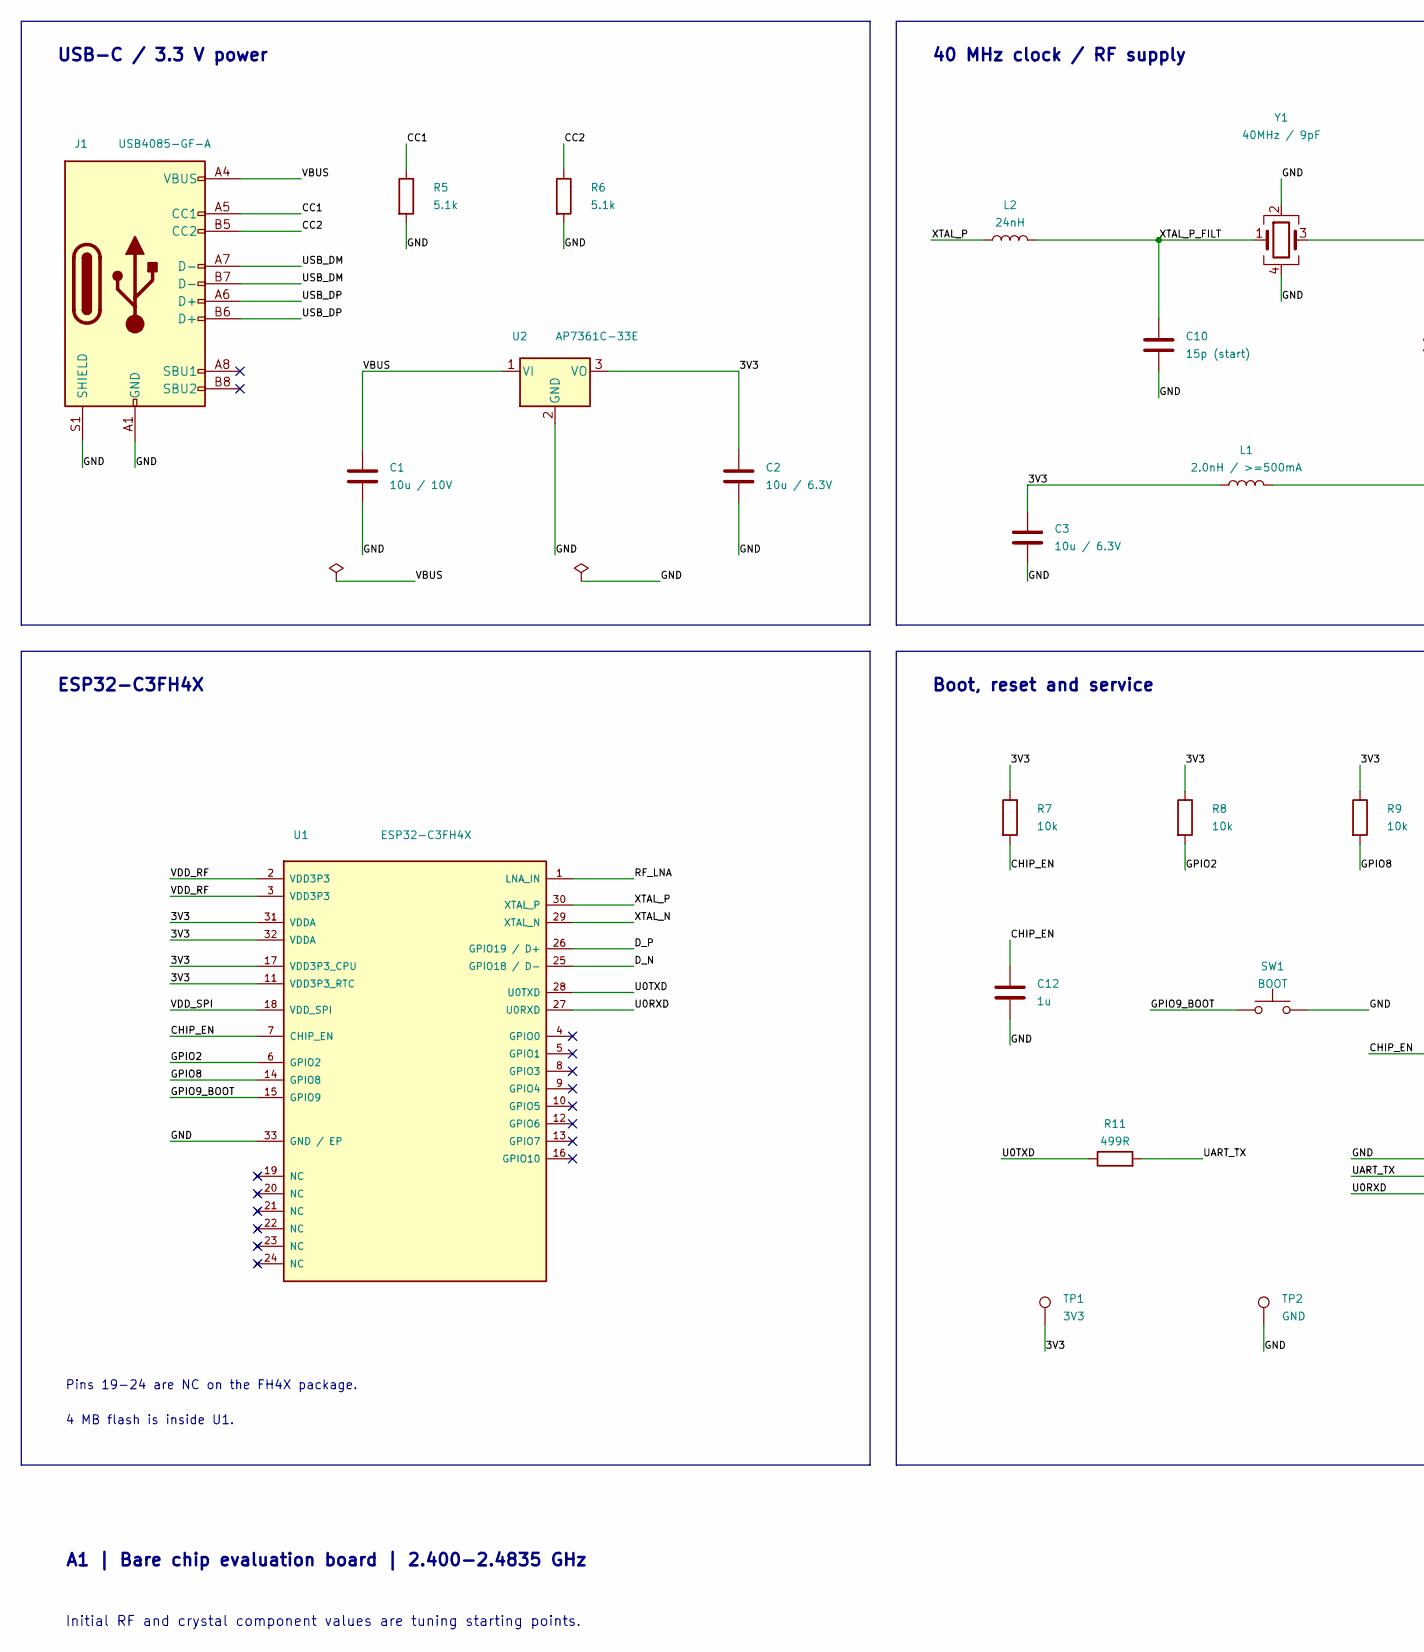
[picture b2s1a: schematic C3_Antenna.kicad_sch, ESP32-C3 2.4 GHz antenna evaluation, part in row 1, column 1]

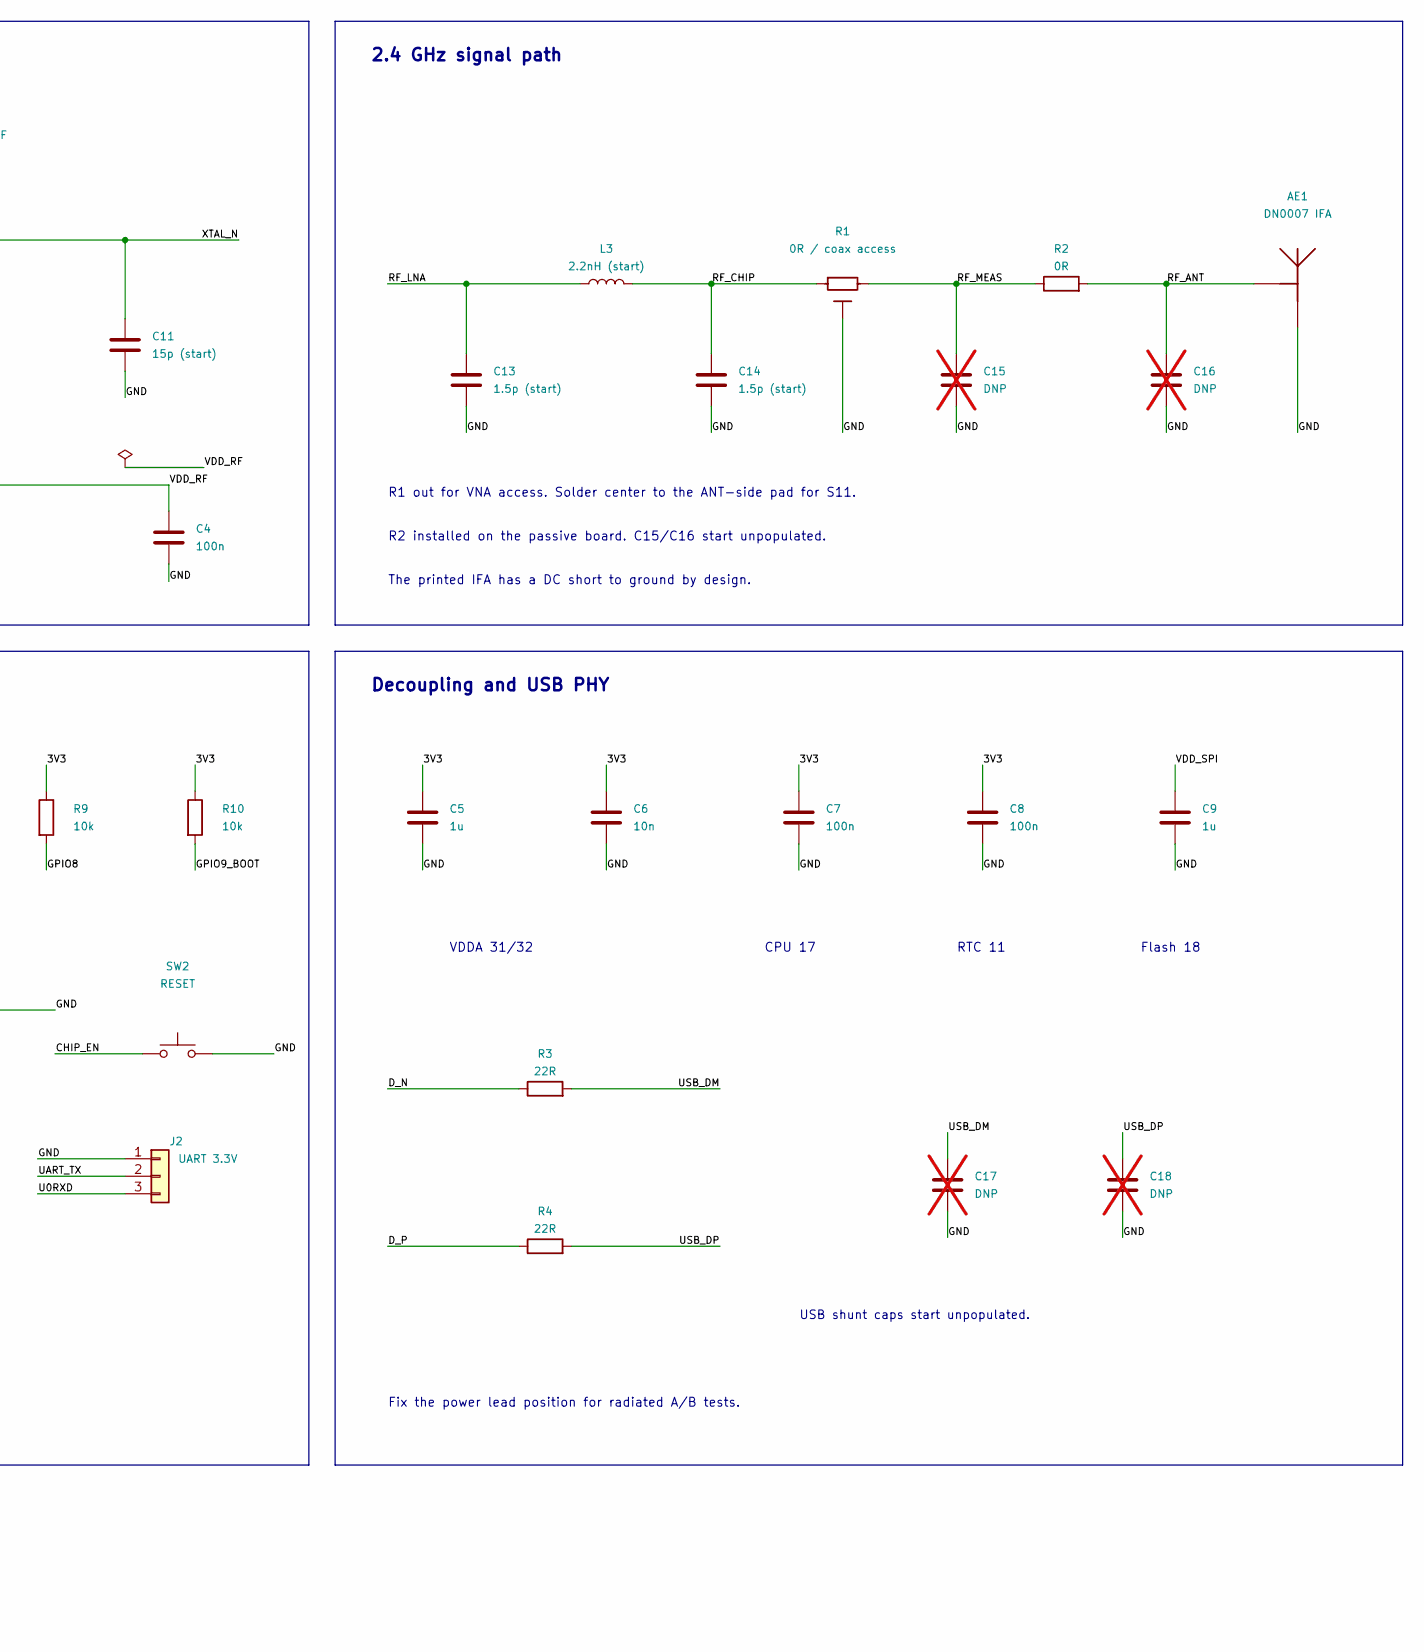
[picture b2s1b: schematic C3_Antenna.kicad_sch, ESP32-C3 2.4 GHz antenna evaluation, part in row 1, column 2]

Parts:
AE1: DN0007 IFA; IFA_DN0007
C1: 10u / 10V; C_0805_2012Metric
C2, C3: 10u / 6.3V; C_0805_2012Metric
C4, C7, C8: 100n; C_0402_1005Metric
C5, C9: 1u; C_0402_1005Metric
C6: 10n; C_0402_1005Metric
C10, C11: 15p (start); C_0402_1005Metric
C12: 1u; C_0603_1608Metric
C13, C14: 1.5p (start); C_0402_1005Metric
C15, C16, C17, C18: DNP; C_0402_1005Metric; not fitted
J1: USB4085-GF-A; USB4085_SilkAtEdge; MPN USB4085-GF-A
J2: UART 3.3V; PinHeader_1x03_P2.54mm_Vertical
L1: 2.0nH / >=500mA; L_0402_1005Metric
L2: 24nH; L_0402_1005Metric
L3: 2.2nH (start); L_0402_1005Metric
R1: 0R / coax access; RF_Link_0603
R2: 0R; R_0402_1005Metric
R3, R4: 22R; R_0402_1005Metric
R5, R6: 5.1k; R_0603_1608Metric
R7, R8, R9, R10: 10k; R_0603_1608Metric
R11: 499R; R_0603_1608Metric
SW1: BOOT; SW_SPST_PTS647_Sx38
SW2: RESET; SW_SPST_PTS647_Sx38
TP1: 3V3; TestPoint_Pad_D1.5mm
TP2: GND; TestPoint_Pad_D1.5mm
U1: ESP32-C3FH4X; QFN32_5x5_MaskedThermalVias; MPN ESP32-C3FH4X
U2: AP7361C-33E; SOT-223-3_TabPin2; MPN AP7361C-33E-13
Y1: 40MHz / 9pF; Crystal_SMD_SeikoEpson_TSX3225-4Pin_3.2x2.5mm; MPN X1E000021017700

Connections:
/3V3: C2.1, C3.1, C5.1, C6.1, C7.1, C8.1, L1.1, R7.1, R8.1, R9.1, R10.1, TP1.1, U1.11 (VDD3P3_RTC), U1.17 (VDD3P3_CPU), U1.31 (VDDA), U1.32 (VDDA), U2.3 (VO)
/CC1: J1.A5 (CC1), R5.1
/CC2: J1.B5 (CC2), R6.1
/CHIP_EN: C12.1, R7.2, SW2.1, U1.7 (CHIP_EN)
/D_N: R3.1, U1.25 (GPIO18_/_D-)
/D_P: R4.1, U1.26 (GPIO19_/_D+)
/GND: AE1.2 (SHORT), C1.2, C2.2, C3.2, C4.2, C5.2, C6.2, C7.2, C8.2, C9.2, C10.2, C11.2, C12.2, C13.2, C14.2, C15.2, C16.2, C17.2, C18.2, J1.A1 (GND), J1.A12 (GND), J1.B1 (GND), J1.B12 (GND), J1.S1 (SHIELD), J2.1, R1.3 (SHIELD), R5.2, R6.2, SW1.2, SW2.2, TP2.1, U1.33 (GND_/_EP), U2.2 (GND), Y1.2, Y1.4
/GPIO2: R8.2, U1.6 (GPIO2)
/GPIO8: R9.2, U1.14 (GPIO8)
/GPIO9_BOOT: R10.2, SW1.1, U1.15 (GPIO9)
/RF_ANT: AE1.1 (FEED), C16.1, R2.2
/RF_CHIP: C14.1, L3.2, R1.1
/RF_LNA: C13.1, L3.1, U1.1 (LNA_IN)
/RF_MEAS: C15.1, R1.2, R2.1
/U0RXD: J2.3, U1.27 (U0RXD)
/U0TXD: R11.1, U1.28 (U0TXD)
/UART_TX: J2.2, R11.2
/USB_DM: C17.1, J1.A7 (D-), J1.B7 (D-), R3.2
/USB_DP: C18.1, J1.A6 (D+), J1.B6 (D+), R4.2
/VBUS: C1.1, J1.A4 (VBUS), J1.A9 (VBUS), J1.B4 (VBUS), J1.B9 (VBUS), U2.1 (VI)
/VDD_RF: C4.1, L1.2, U1.2 (VDD3P3), U1.3 (VDD3P3)
/VDD_SPI: C9.1, U1.18 (VDD_SPI)
/XTAL_N: C11.1, U1.29 (XTAL_N), Y1.3
/XTAL_P: L2.1, U1.30 (XTAL_P)
/XTAL_P_FILT: C10.1, L2.2, Y1.1

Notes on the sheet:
USB-C / 3.3 V power
40 MHz clock / RF supply
2.4 GHz signal path
ESP32-C3FH4X
Boot, reset and service
Decoupling and USB PHY
Pins 19-24 are NC on the FH4X package.
4 MB flash is inside U1.
R1 out for VNA access. Solder center to the ANT-side pad for S11.
R2 installed on the passive board. C15/C16 start unpopulated.
The printed IFA has a DC short to ground by design.
VDDA 31/32
CPU 17
RTC 11
Flash 18
USB shunt caps start unpopulated.
Fix the power lead position for radiated A/B tests.
A1 | Bare chip evaluation board | 2.400-2.4835 GHz
Initial RF and crystal component values are tuning starting points.

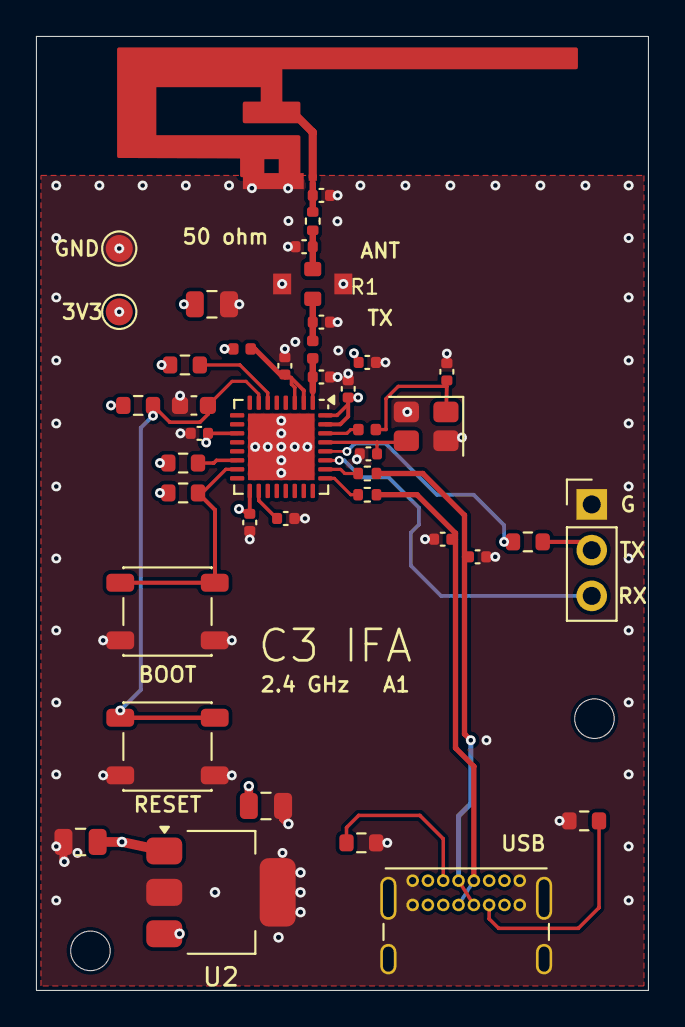
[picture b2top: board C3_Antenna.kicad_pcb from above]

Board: 4 copper layers, 34.0 x 53.0 mm, 44 parts (0 on the bottom side), 25 nets.

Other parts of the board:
H1, H2: MountingHole 2.2mm; MountingHole_2.2mm_M2

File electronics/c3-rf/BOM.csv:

Ref,Value,Footprint,Populate,Part or buying specification,Notes
AE1,DN0007 IFA,C3_RF:IFA_DN0007,NATIVE,Copper feature or test pad,No part
C1,10u / 10V,Capacitor_SMD:C_0805_2012Metric,YES,Murata GRM21BR71C106KE51L,"10 uF / 16 V X7R, 0805."
C2,10u / 6.3V,Capacitor_SMD:C_0805_2012Metric,YES,Murata GRM21BR71C106KE51L,"10 uF / 16 V X7R, 0805."
C3,10u / 6.3V,Capacitor_SMD:C_0805_2012Metric,YES,Murata GRM21BR71C106KE51L,"10 uF / 16 V X7R, 0805."
C4,100n,Capacitor_SMD:C_0402_1005Metric,YES,100n MLCC X5R or X7R,Use footprint package and >=rated voltage
C5,1u,Capacitor_SMD:C_0402_1005Metric,YES,1u MLCC X5R or X7R,Use footprint package and >=rated voltage
C6,10n,Capacitor_SMD:C_0402_1005Metric,YES,10n MLCC X5R or X7R,Use footprint package and >=rated voltage
C7,100n,Capacitor_SMD:C_0402_1005Metric,YES,100n MLCC X5R or X7R,Use footprint package and >=rated voltage
C8,100n,Capacitor_SMD:C_0402_1005Metric,YES,100n MLCC X5R or X7R,Use footprint package and >=rated voltage
C9,1u,Capacitor_SMD:C_0402_1005Metric,YES,1u MLCC X5R or X7R,Use footprint package and >=rated voltage
C10,15p (start),Capacitor_SMD:C_0402_1005Metric,YES,15p 0402 C0G/NP0,Precision RF capacitor. Starting value
C11,15p (start),Capacitor_SMD:C_0402_1005Metric,YES,15p 0402 C0G/NP0,Precision RF capacitor. Starting value
C12,1u,Capacitor_SMD:C_0603_1608Metric,YES,1u MLCC X5R or X7R,Use footprint package and >=rated voltage
C13,1.5p (start),Capacitor_SMD:C_0402_1005Metric,YES,1.5p 0402 C0G/NP0,Precision RF capacitor. Starting value
C14,1.5p (start),Capacitor_SMD:C_0402_1005Metric,YES,1.5p 0402 C0G/NP0,Precision RF capacitor. Starting value
C15,DNP,Capacitor_SMD:C_0402_1005Metric,DNP,Leave empty,Reserved for tuning or measurements
C16,DNP,Capacitor_SMD:C_0402_1005Metric,DNP,Leave empty,Reserved for tuning or measurements
C17,DNP,Capacitor_SMD:C_0402_1005Metric,DNP,Leave empty,Reserved for tuning or measurements
C18,DNP,Capacitor_SMD:C_0402_1005Metric,DNP,Leave empty,Reserved for tuning or measurements
H1,MountingHole 2.2mm,MountingHole:MountingHole_2.2mm_M2,NATIVE,Ø2.2 mm NPTH,M2 carrier screw.
H2,MountingHole 2.2mm,MountingHole:MountingHole_2.2mm_M2,NATIVE,Ø2.2 mm NPTH,M2 carrier screw.
J1,USB4085-GF-A,C3_RF:USB4085_SilkAtEdge,YES,GCT USB4085-GF-A,Orient the opening toward the edge. Solder the plated anchors after reflow.
J2,UART 3.3V,Connector_PinHeader_2.54mm:PinHeader_1x03_P2.54mm_Vertical,YES,Vertical 1x3 2.54 mm male header,"Hand-install. 1 GND, 2 TX, 3 RX, 3.3 V logic"
L1,2.0nH / >=500mA,Inductor_SMD:L_0402_1005Metric,YES,Murata LQW15AN 2.0 nH 0402 rated at least 500 mA,Supply inductor. Low DCR.
L2,24nH,Inductor_SMD:L_0402_1005Metric,YES,Murata LQW15AN24NG00D,"24 nH, 0402. Crystal series inductor."
L3,2.2nH (start),Inductor_SMD:L_0402_1005Metric,YES,Murata LQW15AN 2.2 nH high-Q 0402,Initial RF tuning value.
R1,0R / coax access,C3_RF:RF_Link_0603,YES,0603 0 ohm link,Bridge series pads exclusively. Adjacent pad is coax shield GND
R2,0R,Resistor_SMD:R_0402_1005Metric,YES,0R resistor 1%,Verify package in footprint column
R3,22R,Resistor_SMD:R_0402_1005Metric,YES,22R resistor 1%,Verify package in footprint column
R4,22R,Resistor_SMD:R_0402_1005Metric,YES,22R resistor 1%,Verify package in footprint column
R5,5.1k,Resistor_SMD:R_0603_1608Metric,YES,5.1k resistor 1%,Verify package in footprint column
R6,5.1k,Resistor_SMD:R_0603_1608Metric,YES,5.1k resistor 1%,Verify package in footprint column
R7,10k,Resistor_SMD:R_0603_1608Metric,YES,10k resistor 1%,Verify package in footprint column
R8,10k,Resistor_SMD:R_0603_1608Metric,YES,10k resistor 1%,Verify package in footprint column
R9,10k,Resistor_SMD:R_0603_1608Metric,YES,10k resistor 1%,Verify package in footprint column
R10,10k,Resistor_SMD:R_0603_1608Metric,YES,10k resistor 1%,Verify package in footprint column
R11,499R,Resistor_SMD:R_0603_1608Metric,YES,499R resistor 1%,Verify package in footprint column
SW1,BOOT,Button_Switch_SMD:SW_SPST_PTS647_Sx38,YES,C&K PTS647SM38SMTR2 LFS,"4.5 mm SMT body, 3.8 mm actuator."
SW2,RESET,Button_Switch_SMD:SW_SPST_PTS647_Sx38,YES,C&K PTS647SM38SMTR2 LFS,"4.5 mm SMT body, 3.8 mm actuator."
TP1,3V3,TestPoint:TestPoint_Pad_D1.5mm,NATIVE,Copper feature or test pad,No part
TP2,GND,TestPoint:TestPoint_Pad_D1.5mm,NATIVE,Copper feature or test pad,No part
U1,ESP32-C3FH4X,C3_RF:QFN32_5x5_MaskedThermalVias,YES,Espressif ESP32-C3FH4X,QFN32 with exposed pad and internal 4 MB flash
U2,AP7361C-33E,Package_TO_SOT_SMD:SOT-223-3_TabPin2,YES,Diodes Inc. AP7361C-33E-13,SOT-223. Thermal tab is GND.
Y1,40MHz / 9pF,Crystal:Crystal_SMD_SeikoEpson_TSX3225-4Pin_3.2x2.5mm,YES,Epson X1E000021017700,"40 MHz, CL 9 pF, ±10 ppm. Pins 2 and 4 GND."
